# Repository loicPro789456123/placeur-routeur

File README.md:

# Placeur-routeur

Placeur-routeur automatique de circuits imprimes (Rust + controles Python), en cours de developpement.
Le dossier `PCB_V2/outils/placeur_routage` contient le programme et une carte d'essai.
Les campagnes de test (une graine par machine) sont lancees par `.github/workflows/placeur.yml`;
les resultats arrivent sur la branche `ci-resultats-placeur`.

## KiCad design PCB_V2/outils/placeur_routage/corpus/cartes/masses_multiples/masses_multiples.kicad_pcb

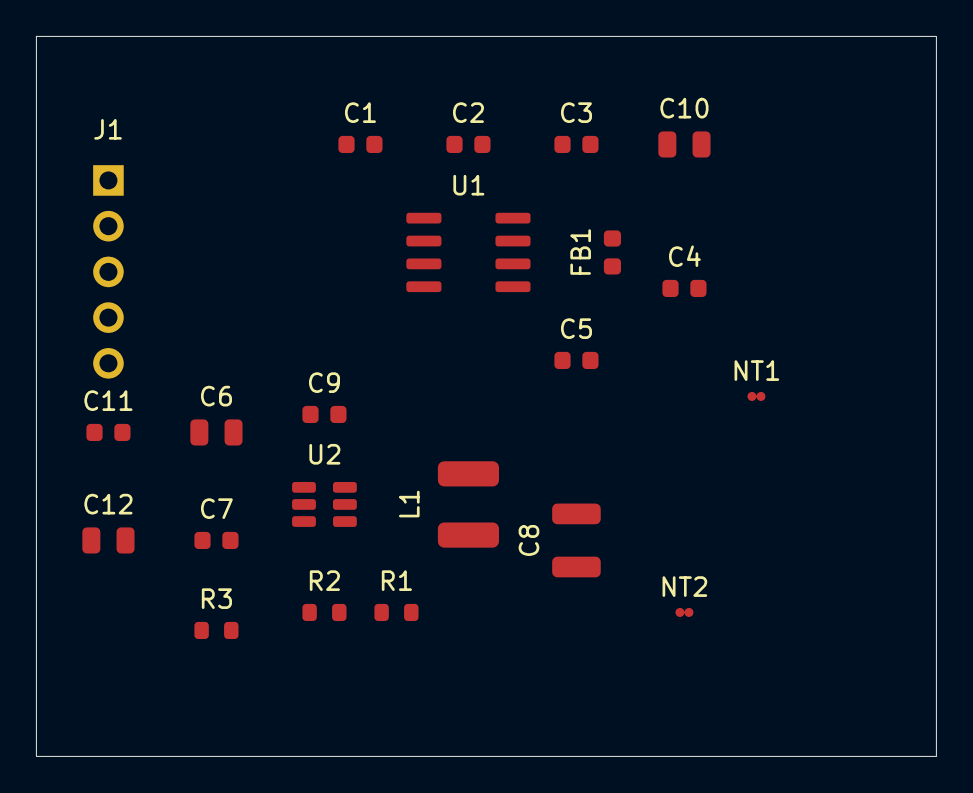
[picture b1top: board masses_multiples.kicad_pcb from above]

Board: 2 copper layers, 50.0 x 40.0 mm, 22 parts (0 on the bottom side), 13 nets, no tracks yet.

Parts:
C1, C2, C4, C9: 100n; C_0603_1608Metric
C3, C7, C11: 1u; C_0603_1608Metric
C5: 10n; C_0603_1608Metric
C6, C10, C12: 10u; C_0805_2012Metric
C8: 22u; C_1210_3225Metric
FB1: Perle ferrite 600R; FB_0603_1608Metric
J1: Barrette; PinHeader_1x05_P2.54mm
L1: 4.7uH; L_4x4
NT1, NT2: Liaison; NetTie-2_SMD_Pad0.5mm
R1: 31k6; R_0603_1608Metric
R2: 10k; R_0603_1608Metric
R3: 100k; R_0603_1608Metric
U1: Microcontroleur; SOIC-8_3.9x4.9mm_P1.27mm
U2: Abaisseur integre; SOT-23-6

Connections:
+3V3: C1.1, C2.1, C3.1, C8.1, C10.1, FB1.1, L1.2, R1.1, U1.1
+5V: C6.1, C7.1, C11.1, C12.1, J1.1, R3.1, U2.5
AGND: C4.2, C5.2, NT1.1, U1.6
AIN: C5.1, J1.5, U1.5
AVDD: C4.1, FB1.2, U1.7
BST: C9.1, U2.1
DGND: C1.2, C2.2, C3.2, C10.2, C11.2, C12.2, J1.2, NT1.2, NT2.2, U1.4, U1.8
EN: R3.2, U2.4
FB: R1.2, R2.1, U2.3
PGND: C6.2, C7.2, C8.2, NT2.1, R2.2, U2.2
SCL: J1.4, U1.3
SDA: J1.3, U1.2
SW: C9.2, L1.1, U2.6

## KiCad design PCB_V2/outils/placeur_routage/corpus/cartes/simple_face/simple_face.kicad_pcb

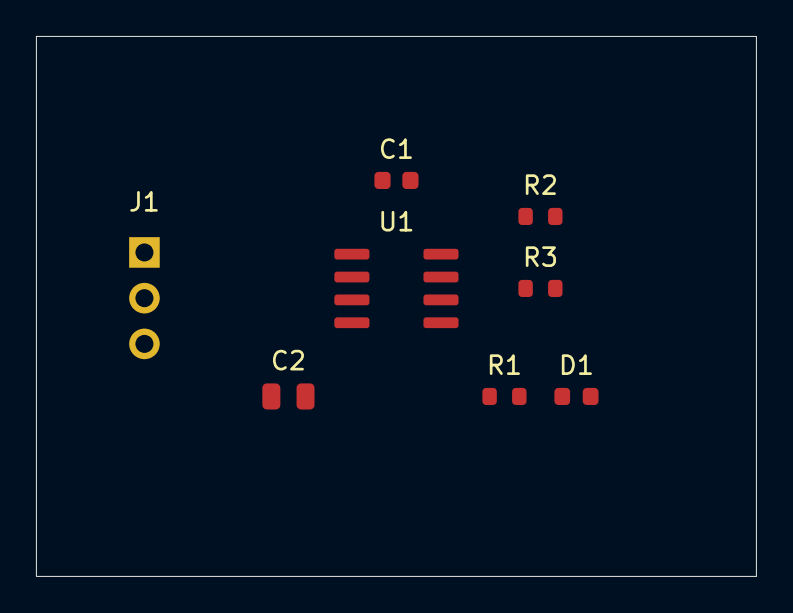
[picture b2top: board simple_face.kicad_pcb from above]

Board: 2 copper layers, 40.0 x 30.0 mm, 8 parts (0 on the bottom side), 7 nets, no tracks yet.

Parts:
C1: 100n; C_0603_1608Metric
C2: 1u; C_0805_2012Metric
D1: Verte; LED_0603_1608Metric
J1: Barrette; PinHeader_1x03_P2.54mm
R1: 330; R_0603_1608Metric
R2, R3: 4k7; R_0603_1608Metric
U1: Microcontroleur; SOIC-8_3.9x4.9mm_P1.27mm

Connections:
+5V: C1.1, C2.1, J1.1, R2.1, R3.1, U1.1
GND: C1.2, C2.2, D1.1, J1.2, U1.4, U1.7, U1.8
IN: J1.3, U1.2
LED: R1.1, U1.3
LED_A: D1.2, R1.2
SCL: R2.2, U1.5
SDA: R3.2, U1.6

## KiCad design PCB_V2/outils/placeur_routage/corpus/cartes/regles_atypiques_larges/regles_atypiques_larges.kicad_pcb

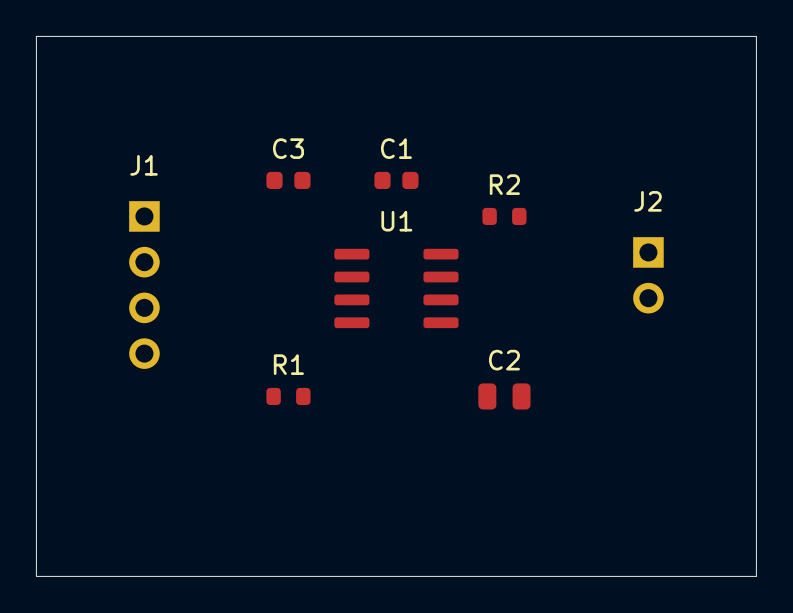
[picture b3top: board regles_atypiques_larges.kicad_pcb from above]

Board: 2 copper layers, 40.0 x 30.0 mm, 8 parts (0 on the bottom side), 8 nets, no tracks yet.

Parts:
C1: 100n; C_0603_1608Metric
C2: 1u; C_0805_2012Metric
C3: 1n; C_0603_1608Metric
J1: Barrette; PinHeader_1x04_P2.54mm
J2: Barrette; PinHeader_1x02_P2.54mm
R1, R2: 1k; R_0603_1608Metric
U1: Porte logique; SOIC-8_3.9x4.9mm_P1.27mm

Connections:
+3V3: C1.1, C2.1, J1.1, J2.1, U1.8
A: R2.2, U1.2
B: C3.1, R1.2, U1.5
GND: C1.2, C2.2, C3.2, J1.2, J2.2, U1.4
IN: J1.3, U1.1
OUT: J1.4, U1.7
Y: R1.1, U1.3
Z: R2.1, U1.6

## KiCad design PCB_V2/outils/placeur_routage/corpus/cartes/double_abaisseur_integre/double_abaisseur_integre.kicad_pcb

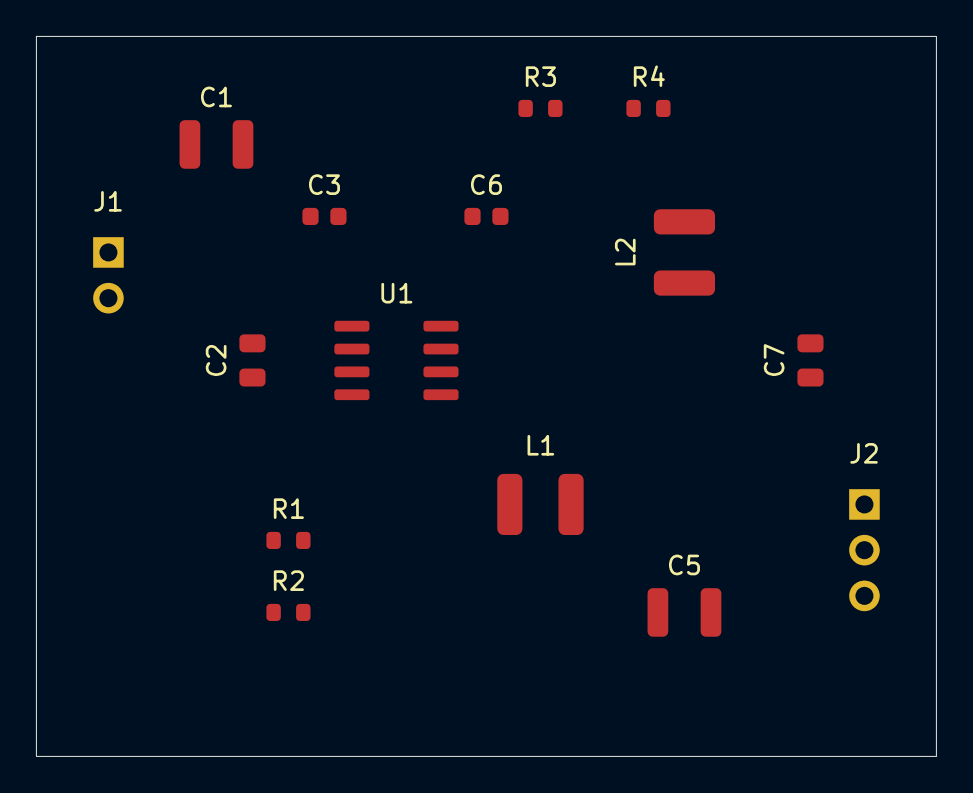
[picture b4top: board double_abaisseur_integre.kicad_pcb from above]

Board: 2 copper layers, 50.0 x 40.0 mm, 15 parts (0 on the bottom side), 10 nets, no tracks yet.

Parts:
C1, C5: 22u; C_1210_3225Metric
C2: 1u; C_0805_2012Metric
C3, C6: 100n; C_0603_1608Metric
C7: 10u; C_0805_2012Metric
J1: Barrette; PinHeader_1x02_P2.54mm
J2: Barrette; PinHeader_1x03_P2.54mm
L1: 4.7uH; L_4x4
L2: 2.2uH; L_4x4
R1: 52k3; R_0603_1608Metric
R2, R4: 10k; R_0603_1608Metric
R3: 31k6; R_0603_1608Metric
U1: Abaisseur double integre; SOIC-8_3.9x4.9mm_P1.27mm

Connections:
+3V3: C7.1, J2.2, L2.2, R3.1
+5V: C5.1, J2.1, L1.2, R1.1
+12V: C1.1, C2.1, J1.1, U1.1
BST1: C3.1, U1.3
BST2: C6.1, U1.7
FB1: R1.2, R2.1, U1.5
FB2: R3.2, R4.1, U1.8
GND: C1.2, C2.2, C5.2, C7.2, J1.2, J2.3, R2.2, R4.2, U1.4
SW1: C3.2, L1.1, U1.2
SW2: C6.2, L2.1, U1.6

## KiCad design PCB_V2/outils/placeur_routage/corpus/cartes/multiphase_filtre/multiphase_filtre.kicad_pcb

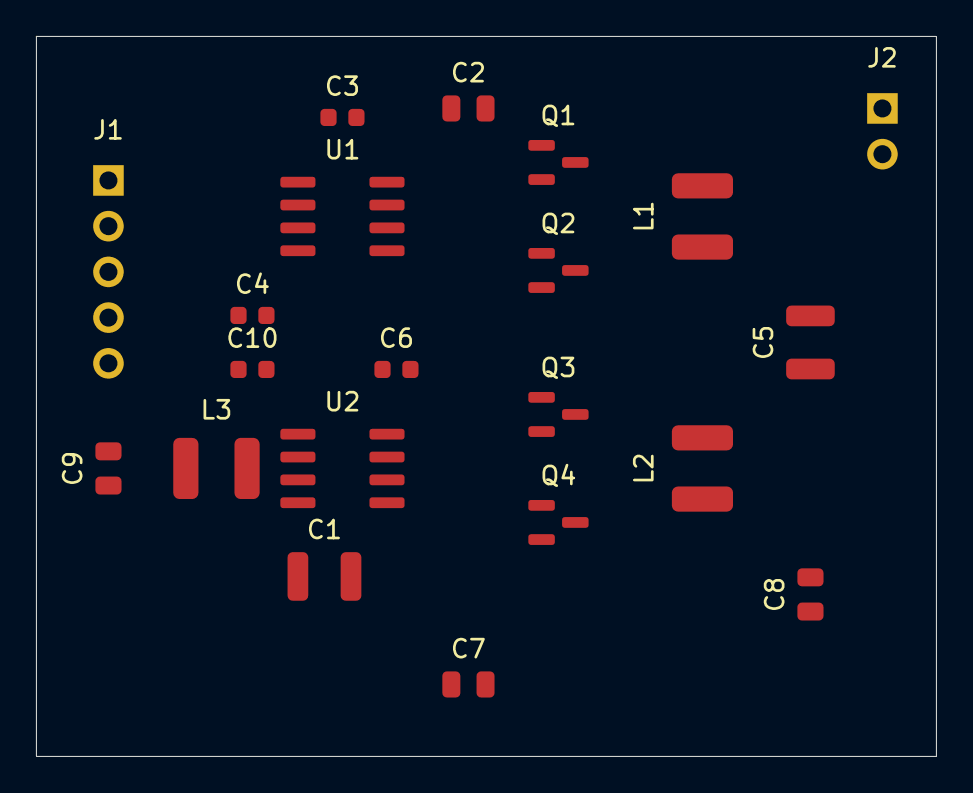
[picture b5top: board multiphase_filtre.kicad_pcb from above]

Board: 2 copper layers, 50.0 x 40.0 mm, 21 parts (0 on the bottom side), 15 nets, no tracks yet.

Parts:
C1, C5: 22u; C_1210_3225Metric
C2, C7, C9: 1u; C_0805_2012Metric
C3, C6: 100n; C_0603_1608Metric
C4, C10: 1u; C_0603_1608Metric
C8: 4u7; C_0805_2012Metric
J1: Barrette; PinHeader_1x05_P2.54mm
J2: Barrette; PinHeader_1x02_P2.54mm
L1, L2: 4.7uH; L_4x4
L3: 1uH; L_4x4
Q1, Q2, Q3, Q4: MOSFET N; SOT-23
U1, U2: Pilote demi-pont; SOIC-8_3.9x4.9mm_P1.27mm

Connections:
+5V: C5.1, C8.1, J2.1, L1.2, L2.2
+12V: C1.1, C2.1, C7.1, L3.2, Q1.3, Q3.3
+12V_IN: C9.1, J1.1, L3.1
GH1: Q1.1, U1.7
GH2: Q3.1, U2.7
GL1: Q2.1, U1.5
GL2: Q4.1, U2.5
GND: C1.2, C2.2, C4.2, C5.2, C7.2, C8.2, C9.2, C10.2, J1.2, J2.2, Q2.2, Q4.2, U1.4, U2.4
HB1: C3.1, U1.8
HB2: C6.1, U2.8
PWM1: J1.4, U1.2
PWM2: J1.5, U2.2
SW1: C3.2, L1.1, Q1.2, Q2.3, U1.6
SW2: C6.2, L2.1, Q3.2, Q4.3, U2.6
VDRV: C4.1, C10.1, J1.3, U1.1, U1.3, U2.1, U2.3

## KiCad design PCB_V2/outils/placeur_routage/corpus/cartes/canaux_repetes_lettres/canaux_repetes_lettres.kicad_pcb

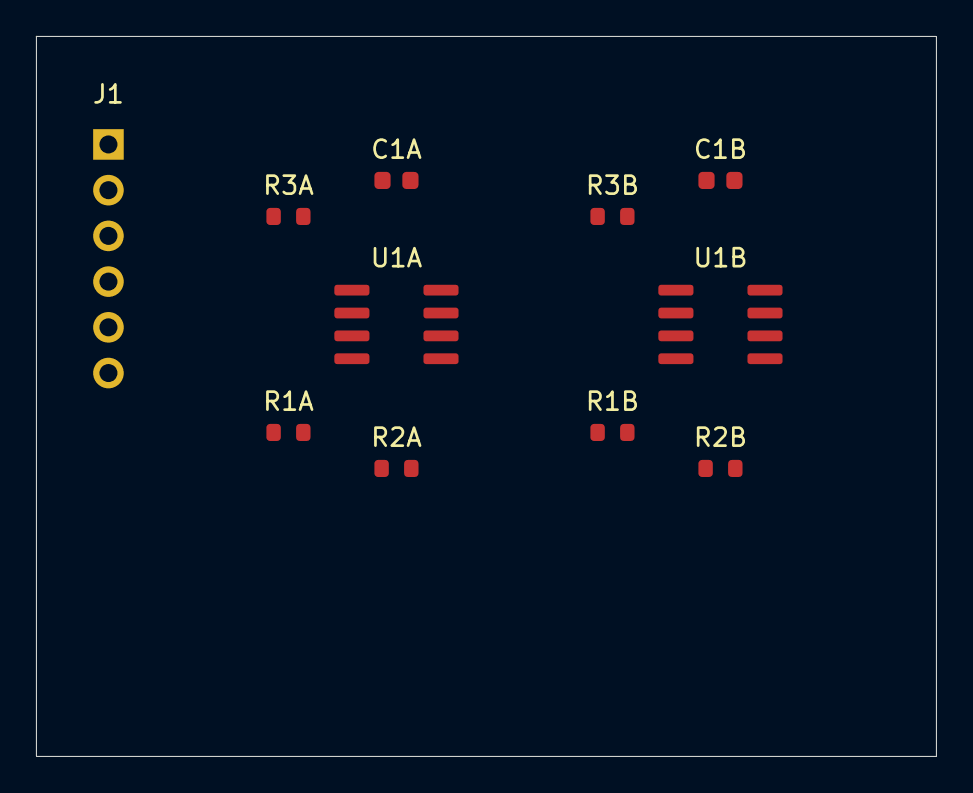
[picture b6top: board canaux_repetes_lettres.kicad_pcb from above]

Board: 2 copper layers, 50.0 x 40.0 mm, 11 parts (0 on the bottom side), 10 nets, no tracks yet.

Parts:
C1A, C1B: 100n; C_0603_1608Metric
J1: Barrette; PinHeader_1x06_P2.54mm
R1A, R1B, R3A, R3B: 1k; R_0603_1608Metric
R2A, R2B: 10k; R_0603_1608Metric
U1A, U1B: Amplificateur; SOIC-8_3.9x4.9mm_P1.27mm

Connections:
+5V: C1A.1, C1B.1, J1.1, U1A.8, U1B.8
GND: C1A.2, C1B.2, J1.2, R3A.2, R3B.2, U1A.4, U1B.4
INA: J1.3, R1A.1
INB: J1.5, R1B.1
INNA: R2A.1, R3A.1, U1A.2
INNB: R2B.1, R3B.1, U1B.2
INPA: R1A.2, U1A.3
INPB: R1B.2, U1B.3
OUTA: J1.4, R2A.2, U1A.1
OUTB: J1.6, R2B.2, U1B.1

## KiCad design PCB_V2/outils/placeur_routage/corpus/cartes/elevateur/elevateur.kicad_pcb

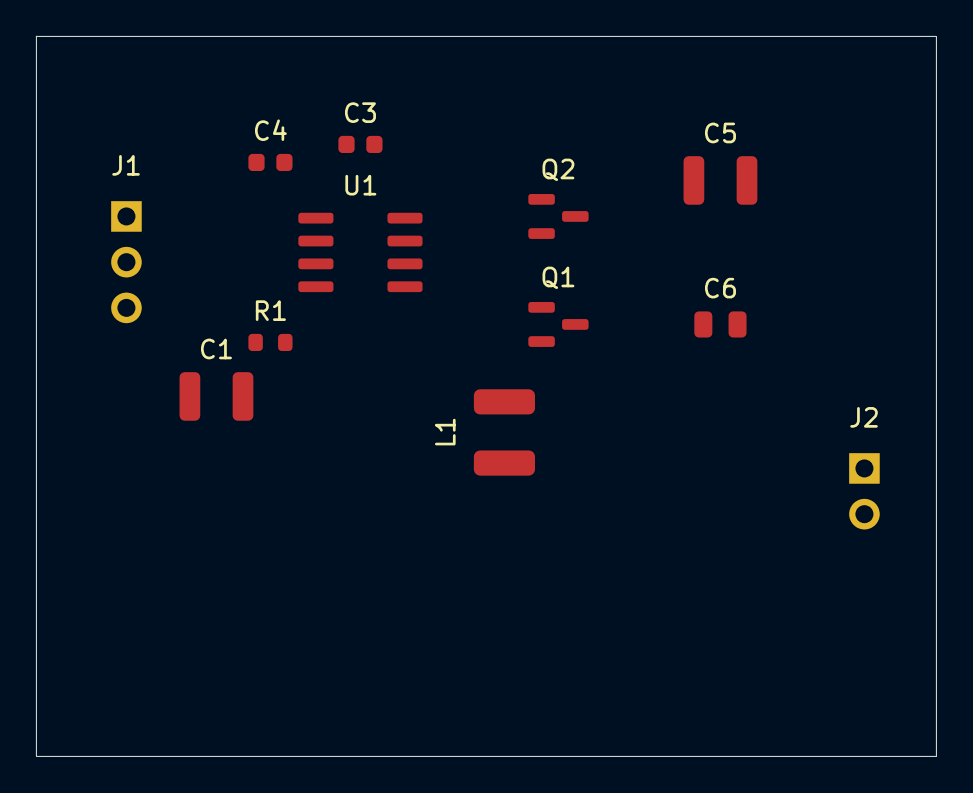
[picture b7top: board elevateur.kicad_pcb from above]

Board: 2 copper layers, 50.0 x 40.0 mm, 12 parts (0 on the bottom side), 9 nets, no tracks yet.

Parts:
C1, C5: 22u; C_1210_3225Metric
C3: 100n; C_0603_1608Metric
C4: 1u; C_0603_1608Metric
C6: 1u; C_0805_2012Metric
J1: Barrette; PinHeader_1x03_P2.54mm
J2: Barrette; PinHeader_1x02_P2.54mm
L1: 4.7uH; L_4x4
Q1, Q2: MOSFET N; SOT-23
R1: 100k; R_0603_1608Metric
U1: Pilote demi-pont; SOIC-8_3.9x4.9mm_P1.27mm

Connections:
+5V: C1.1, C4.1, J1.1, L1.1, R1.1, U1.1
+12V: C5.1, C6.1, J2.1, Q2.3
EN: R1.2, U1.3
GH: Q2.1, U1.7
GL: Q1.1, U1.5
GND: C1.2, C4.2, C5.2, C6.2, J1.2, J2.2, Q1.2, U1.4
HB: C3.1, U1.8
PWM: J1.3, U1.2
SW: C3.2, L1.2, Q1.3, Q2.2, U1.6

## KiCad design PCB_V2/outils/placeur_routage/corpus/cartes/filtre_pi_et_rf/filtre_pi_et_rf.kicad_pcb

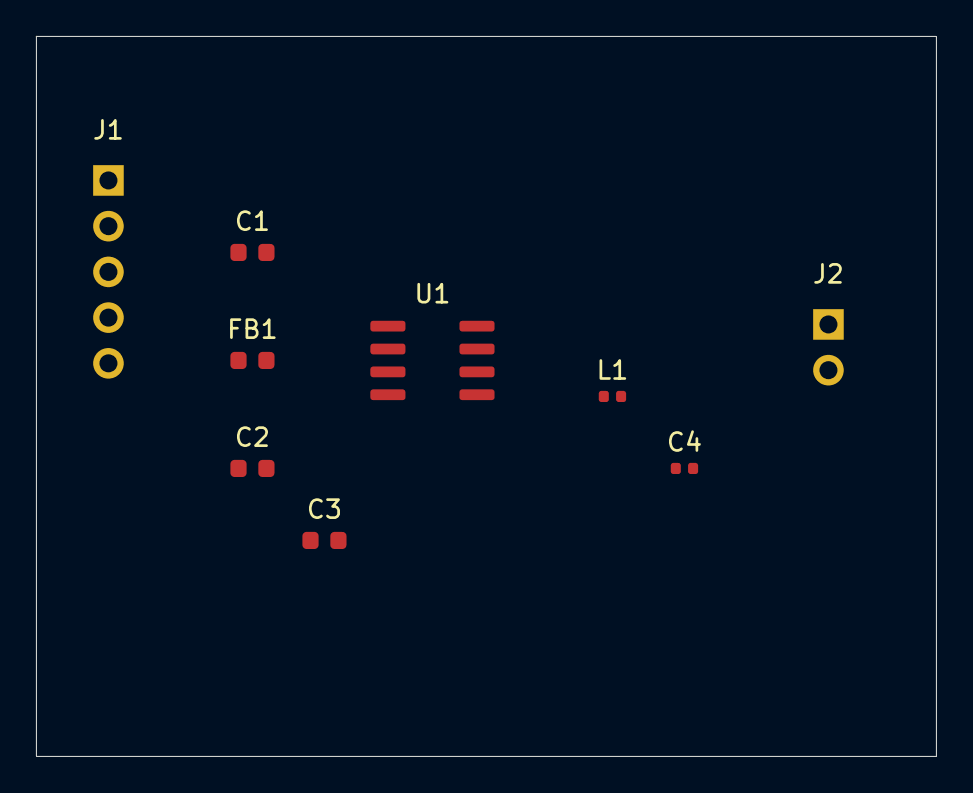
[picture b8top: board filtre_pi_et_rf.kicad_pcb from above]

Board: 2 copper layers, 50.0 x 40.0 mm, 9 parts (0 on the bottom side), 8 nets, no tracks yet.

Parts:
C1, C2: 1u; C_0603_1608Metric
C3: 100n; C_0603_1608Metric
C4: 1p; C_0402_1005Metric
FB1: Perle ferrite 600R; FB_0603_1608Metric
J1: Barrette; PinHeader_1x05_P2.54mm
J2: Barrette; PinHeader_1x02_P2.54mm
L1: 2.2nH; L_0402_1005Metric
U1: Emetteur radio; SOIC-8_3.9x4.9mm_P1.27mm

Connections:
+3V3: C1.1, FB1.1, J1.1, U1.1
AIN: J1.5, U1.7
ANT: C4.1, J2.1, L1.2
AVDD: C2.1, C3.1, FB1.2, U1.2
GND: C1.2, C2.2, C3.2, C4.2, J1.2, J2.2, U1.4, U1.8
RF_OUT: L1.1, U1.3
SCL: J1.4, U1.6
SDA: J1.3, U1.5
